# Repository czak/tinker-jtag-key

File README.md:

# tinker-jtag-key

JTAG breakout board for ASUS Tinker Board.
Plugs into the MicroSD card socket and exposes the JTAG signals on a standard 20-pin footprint. 

## Note

**First prototype, not tested!**

## Preview

## References

* Inspired by [SparkFun MicroSD Sniffer](https://github.com/sparkfun/MicroSD_Sniffer)
  * Micro SD card footprint & overall PCB layout
* MicroSD socket footprint from Joan_Sparky at [KiCad Info forum](https://forum.kicad.info/t/microsd-component-footprint-help/3095/5)

## License

https://creativecommons.org/licenses/by-sa/4.0/

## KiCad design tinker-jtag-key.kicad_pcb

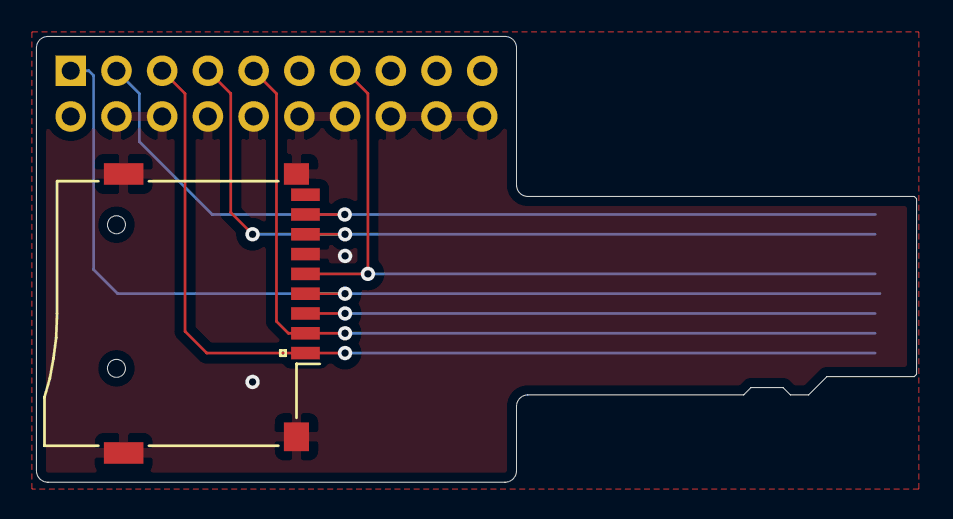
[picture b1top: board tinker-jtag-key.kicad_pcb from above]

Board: 2 copper layers, 48.9 x 24.8 mm, 3 parts (1 on the bottom side), 8 nets.

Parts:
J1: 112J-TXAR-R01; MicroSD_Card_Socket
J2: Conn_ARM_JTAG_SWD_20; PinHeader_2x10_P2.54mm_Vertical
P1: Micro_SD_Card; MicroSD_Card_Pins

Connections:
/CD-DAT3: J1.2, J2.9, P1.2
/CLK: J1.5, J2.13, P1.5
/CMD: J1.3, P1.3
/DAT0: J1.7, J2.7, P1.7
/DAT1: J1.8, J2.3, P1.8
/DAT2: J1.1, J2.5, P1.1
GND: J1.6, J2.4, J2.6, J2.8, J2.10, J2.12, J2.14, J2.16, J2.18, J2.20, P1.6
VDD: J1.4, J2.1, P1.4

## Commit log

2020-05-15 Add front & back renders
2020-05-15 Fix typo
2020-05-15 Create LICENSE
2020-05-15 Set min mask width to 0
2021-04-30 Add microSD socket datasheet
2021-04-30 Cleanup, fix GND fill; draw notch silkscreen
